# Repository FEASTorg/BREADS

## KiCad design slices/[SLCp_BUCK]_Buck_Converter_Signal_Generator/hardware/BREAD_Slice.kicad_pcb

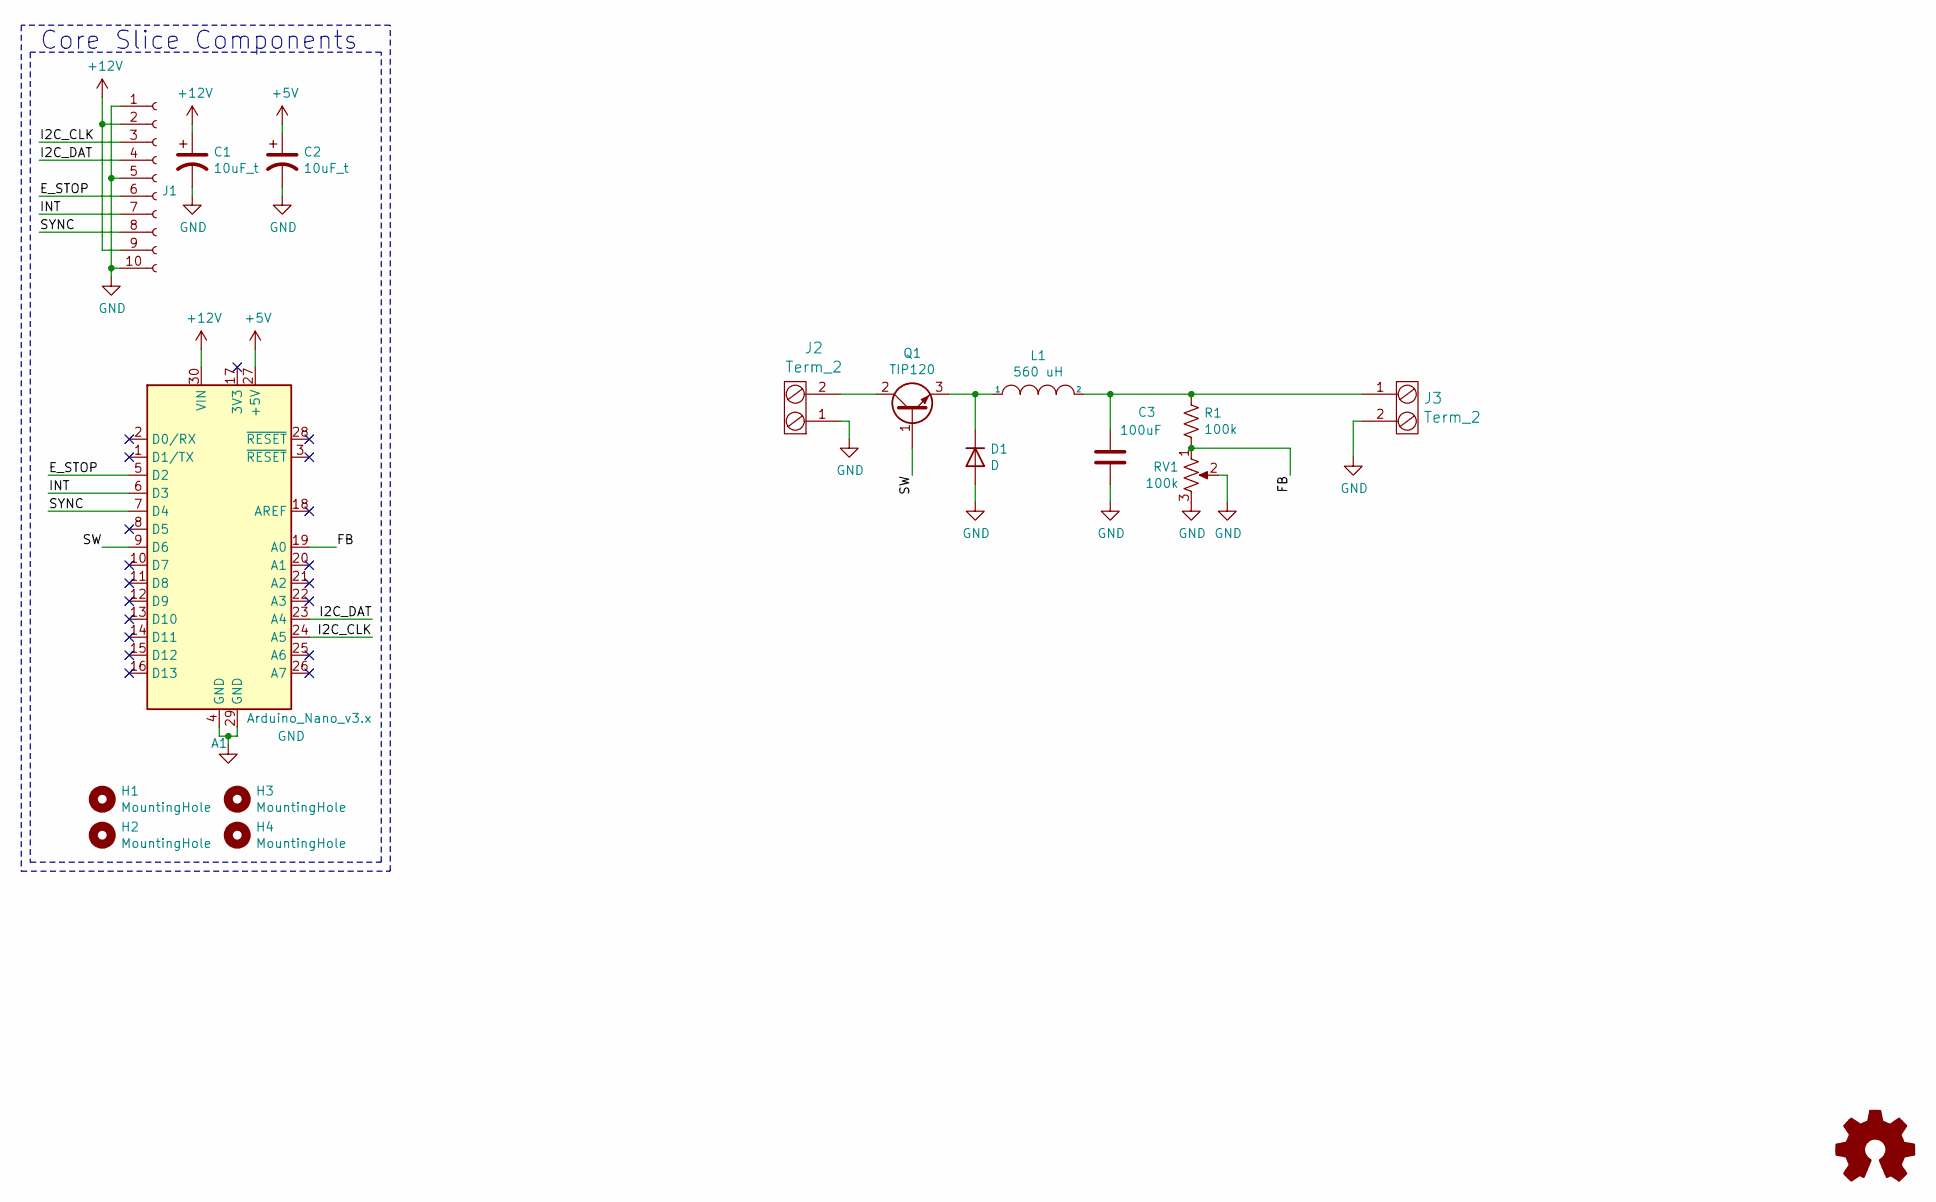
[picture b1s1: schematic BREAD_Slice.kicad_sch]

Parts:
A1: Arduino_Nano_v3.x; Arduino_Nano
C1, C2: 10uF_t; C_2312; Part # T491C106K025AT
C3: 100uF; C_Radial_D8_L11.5_P3.5
D1: D; Diode_DO-41_SOD81_Horizontal_RM10
H1, H2, H3, H4: MountingHole; MountingHole_3.2mm_M3_DIN965_Pad
J1: Conn_01x10_Female; PinSocket_1x10_P2.54mm_Horizontal
J2, J3: Term_2; TerminalBlock_Pheonix_MKDS1.5-2pol; Part # 1935161
L1: 560 uH; L_Radial_D28.0mm_P29.20mm
Logo1: Logo_Open_Hardware_Small; OSHW-Symbol_6.7x6mm_SilkScreen
Q1: TIP120; TO-220_Neutral123_Vertical_LargePads; Part # TIP120
R1: 100k; R_Axial_DIN0309_L9.0mm_D3.2mm_P15.24mm_Horizontal
RV1: 100k; Potentiometer_Bourns_3266W_Vertical

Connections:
+5V: A1.27 (+5V), C2.1
+12V: A1.30 (VIN), C1.1, J1.2, J1.9
/E_STOP: A1.5 (D2), J1.6
/FB: A1.19 (A0), R1.2, RV1.1
/I2C_CLK: A1.24 (A5), J1.3
/I2C_DAT: A1.23 (A4), J1.4
/INT: A1.6 (D3), J1.7
/SW: A1.9 (D6), Q1.1 (B)
/SYNC: A1.7 (D4), J1.8
GND: A1.4 (GND), A1.29 (GND), C1.2, C2.2, C3.2, D1.2 (A), J1.1, J1.5, J1.10, J2.1, J3.2, RV1.2, RV1.3
unnamed: C3.1, J3.1, L1.2, R1.1
unnamed: D1.1 (K), L1.1, Q1.3 (E)
unnamed: J2.2, Q1.2 (C)

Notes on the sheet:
Core Slice Components

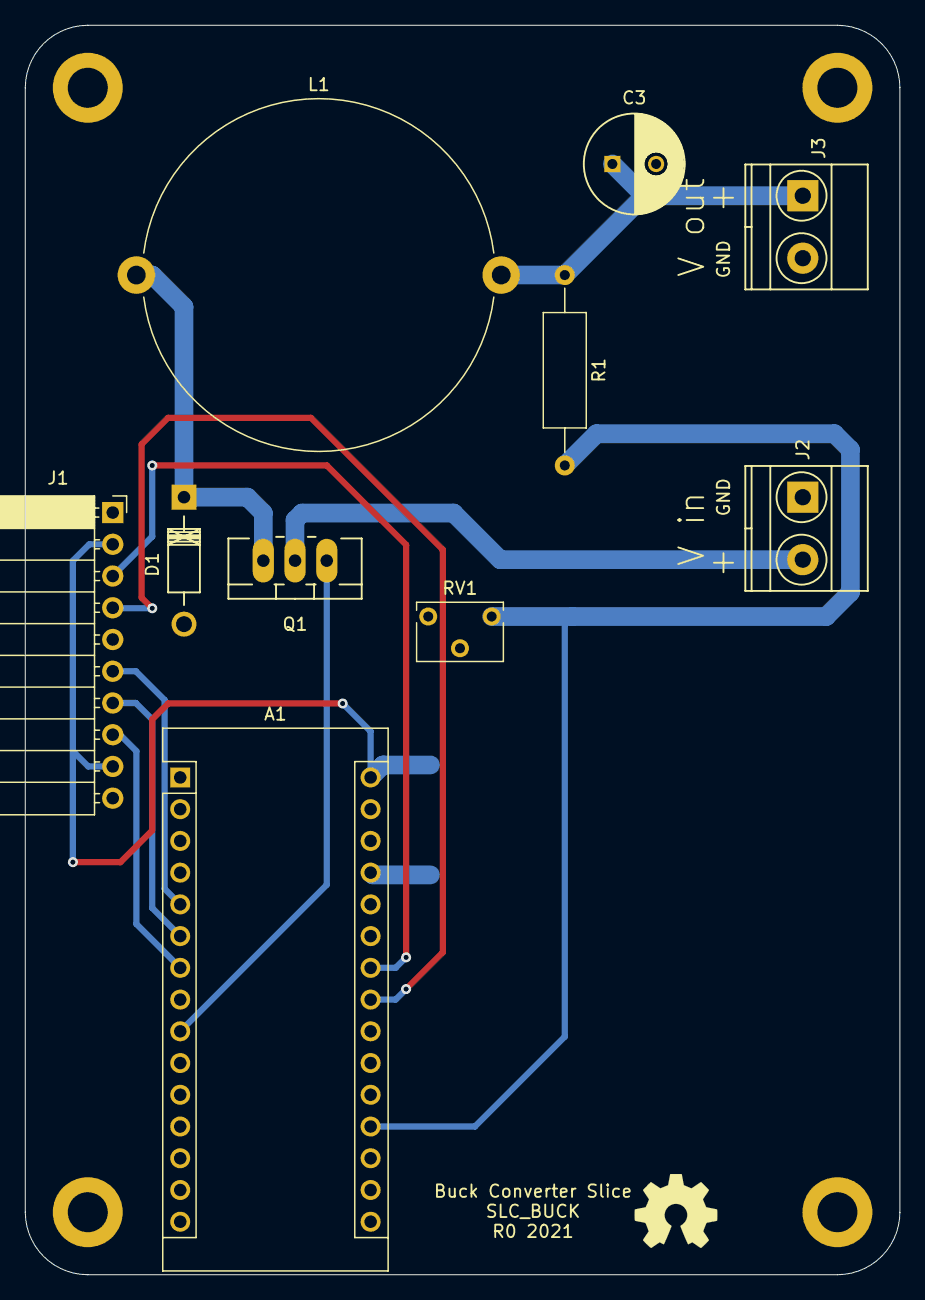
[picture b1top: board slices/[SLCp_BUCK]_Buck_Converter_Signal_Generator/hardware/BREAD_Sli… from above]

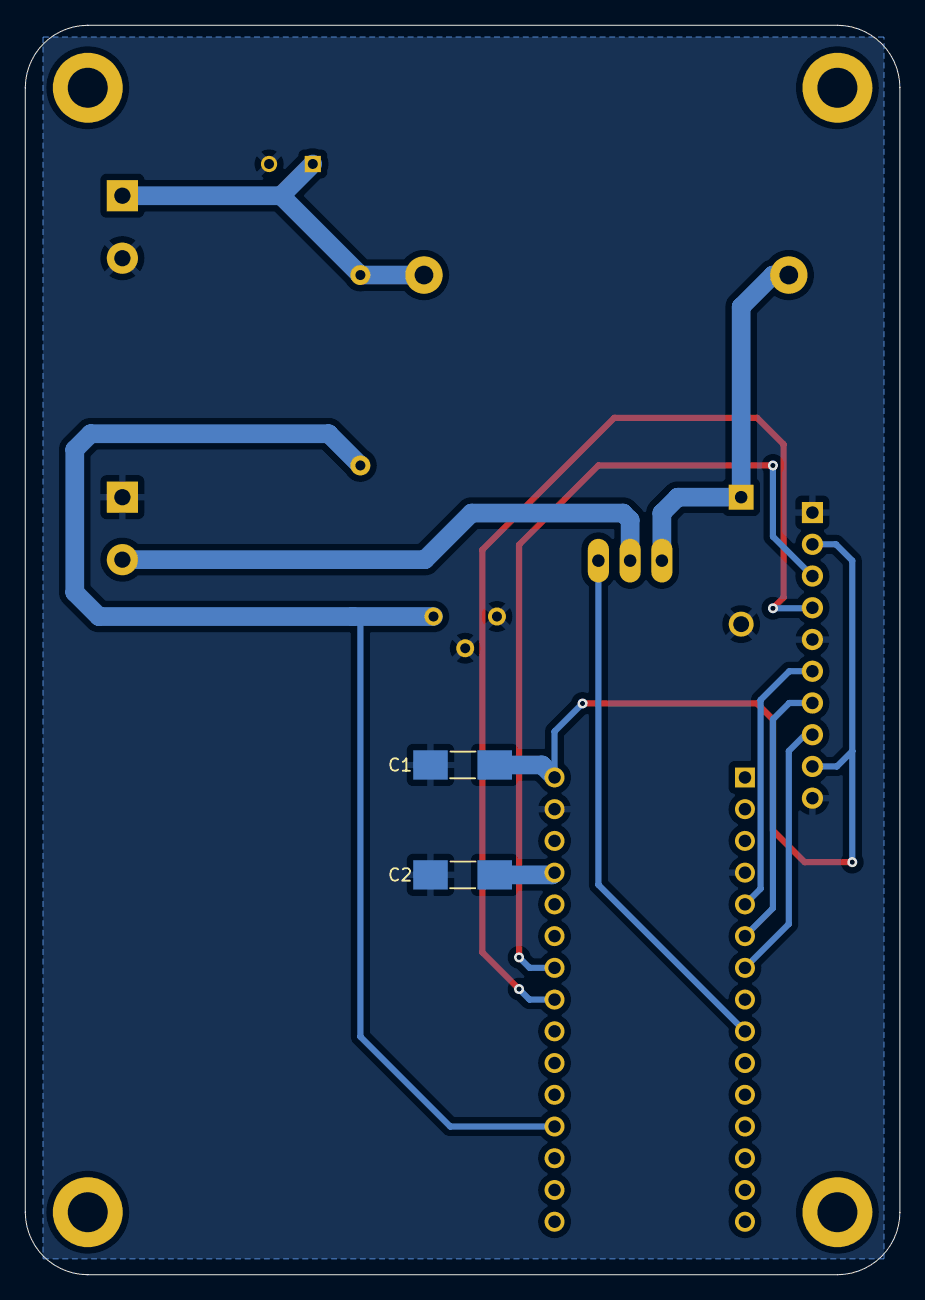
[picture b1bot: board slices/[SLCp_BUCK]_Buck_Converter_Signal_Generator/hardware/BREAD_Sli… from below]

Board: 2 copper layers, 70.0 x 100.0 mm, 17 parts (2 on the bottom side), 13 nets.

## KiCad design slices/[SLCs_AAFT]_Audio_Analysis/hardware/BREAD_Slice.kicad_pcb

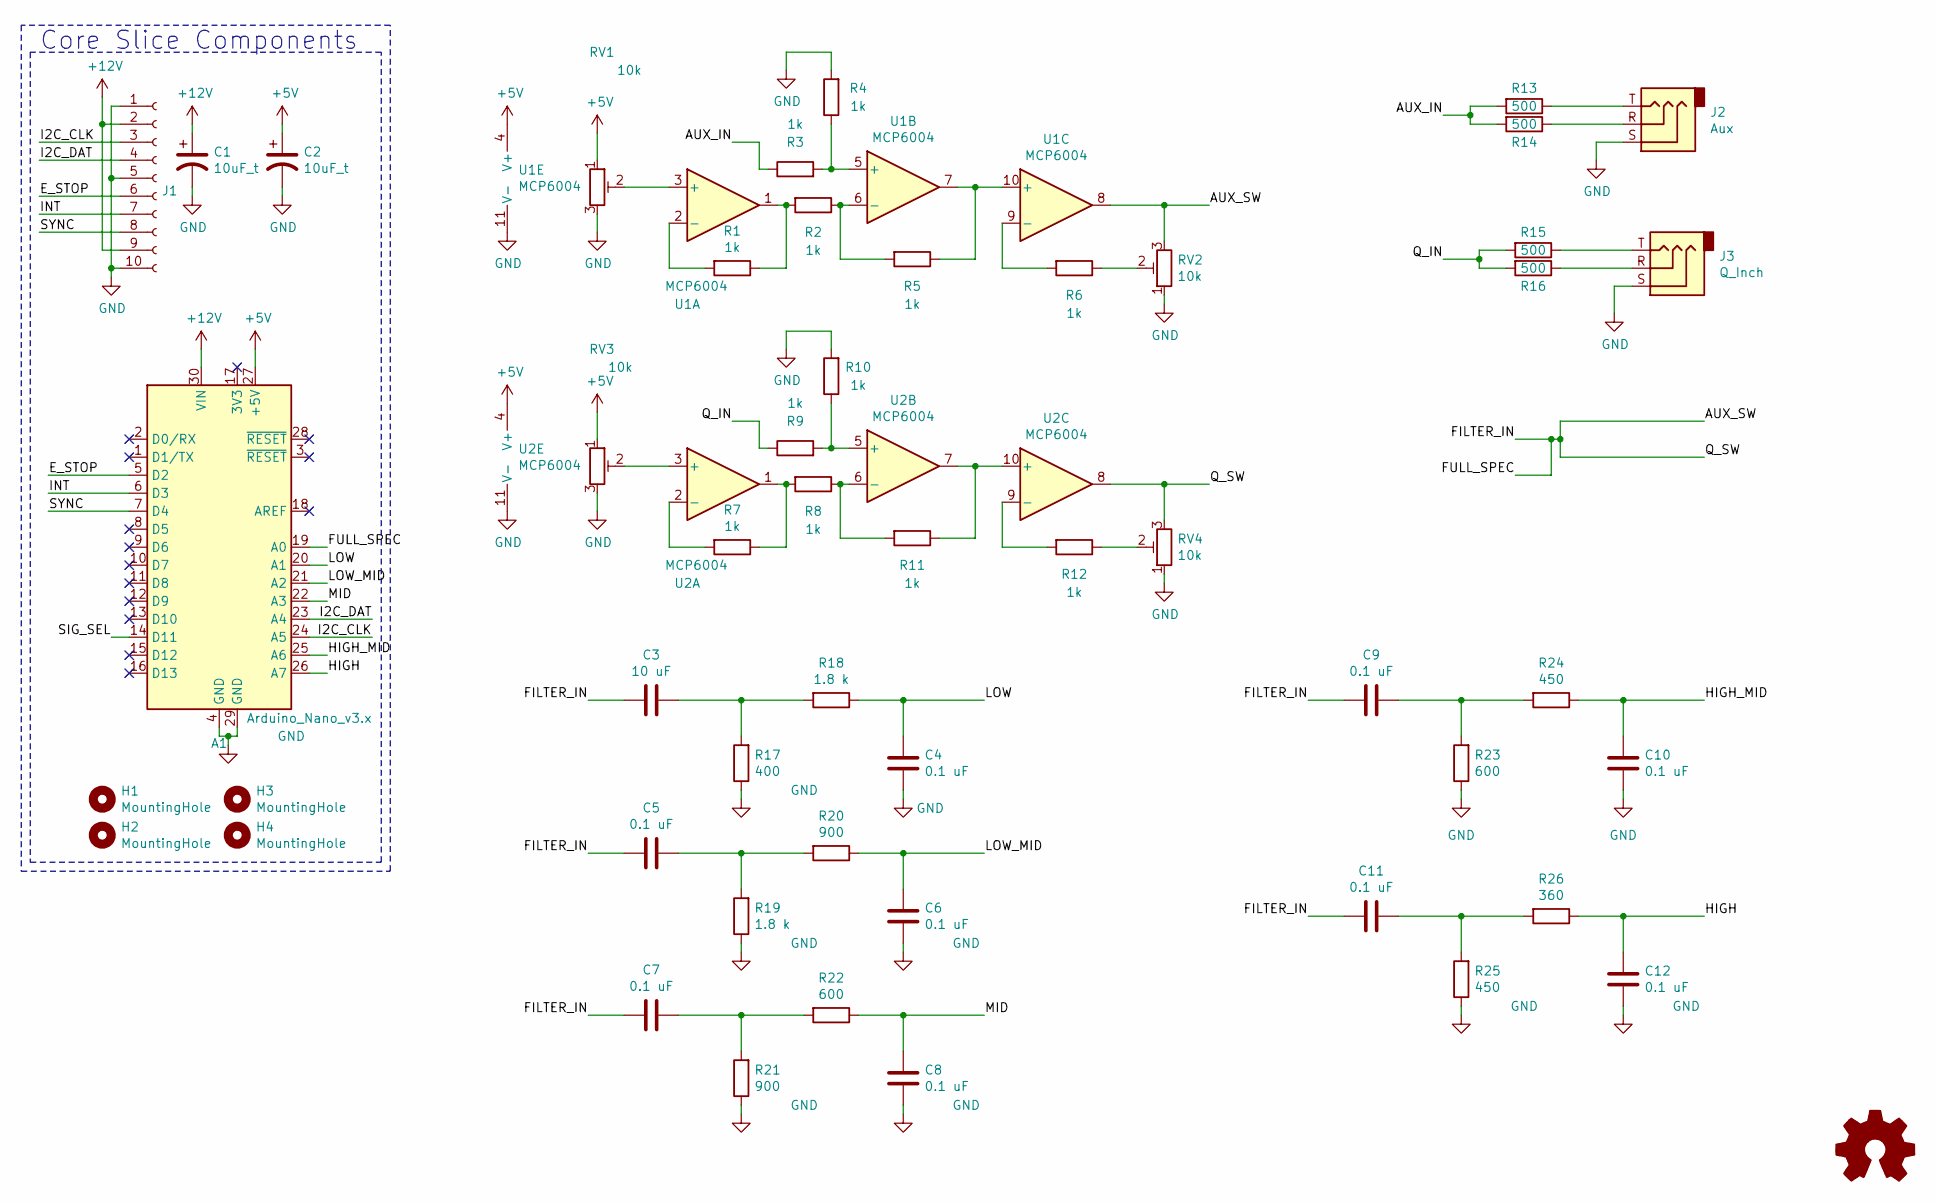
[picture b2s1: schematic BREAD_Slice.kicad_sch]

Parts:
A1: Arduino_Nano_v3.x; Arduino_Nano
C1, C2: 10uF_t; C_2312; Part # T491C106K025AT
C3: 10 uF; C_1206_3216Metric_Pad1.33x1.80mm_HandSolder
C4, C5, C6, C7, C8, C9, C10, C11, C12: 0.1 uF; C_1206_3216Metric_Pad1.33x1.80mm_HandSolder
H1, H2, H3, H4: MountingHole; MountingHole_3.2mm_M3_DIN965_Pad
J1: Conn_01x10_Female; PinSocket_1x10_P2.54mm_Horizontal
J2: Aux; Jack_3.5mm_CUI_SJ1-3533NG_Horizontal
J3: Q_Inch; Jack_6.35mm_Neutrik_NMJ6HCD2_Horizontal
Logo1: Logo_Open_Hardware_Small; OSHW-Symbol_6.7x6mm_SilkScreen
R1, R2, R3, R4, R5, R6, R7, R8, R9, R10, R11, R12: 1k; R_1206_3216Metric_Pad1.30x1.75mm_HandSolder
R13, R14, R15, R16: 500; R_1206_3216Metric_Pad1.30x1.75mm_HandSolder
R17: 400; R_1206_3216Metric_Pad1.30x1.75mm_HandSolder
R18, R19: 1.8 k; R_1206_3216Metric_Pad1.30x1.75mm_HandSolder
R20, R21: 900; R_1206_3216Metric_Pad1.30x1.75mm_HandSolder
R22, R23: 600; R_1206_3216Metric_Pad1.30x1.75mm_HandSolder
R24, R25: 450; R_1206_3216Metric_Pad1.30x1.75mm_HandSolder
R26: 360; R_1206_3216Metric_Pad1.30x1.75mm_HandSolder
RV1, RV2, RV3, RV4: 10k; Potentiometer_Bourns_3266W_Vertical
U1, U2: MCP6004; DIP-14_W7.62mm_Socket

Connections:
+5V: A1.27 (+5V), C2.1, RV1.1, RV3.1, U1.4 (V+), U2.4 (V+)
+12V: A1.30 (VIN), C1.1, J1.2, J1.9
/AUX_IN: R3.1, R13.2, R14.2
/AUX_SW: A1.19 (A0), C3.2, C5.2, C7.2, C9.2, C11.2, RV2.3, RV4.3, U1.8, U2.8
/E_STOP: A1.5 (D2), J1.6
/HIGH: A1.26 (A7), C12.2, R26.1
/HIGH_MID: A1.25 (A6), C10.2, R24.1
/I2C_CLK: A1.24 (A5), J1.3
/I2C_DAT: A1.23 (A4), J1.4
/INT: A1.6 (D3), J1.7
/LOW: A1.20 (A1), C4.2, R18.1
/LOW_MID: A1.21 (A2), C6.2, R20.1
/MID: A1.22 (A3), C8.2, R22.1
/Q_IN: R9.1, R15.2, R16.2
/SIG_SEL: A1.14 (D11)
/SYNC: A1.7 (D4), J1.8
GND: A1.4 (GND), A1.29 (GND), C1.2, C2.2, C4.1, C6.1, C8.1, C10.1, C12.1, J1.1, J1.5, J1.10, J2.S, J3.S, R4.2, R10.2, R17.1, R19.1, R21.1, R23.1, R25.1, RV1.3, RV2.1, RV3.3, RV4.1, U1.11 (V-), U2.11 (V-)
unnamed: C3.1, R17.2, R18.2
unnamed: C5.1, R19.2, R20.2
unnamed: C7.1, R21.2, R22.2
unnamed: C9.1, R23.2, R24.2
unnamed: C11.1, R25.2, R26.2
unnamed: J2.R, R14.1
unnamed: J2.T, R13.1
unnamed: J3.R, R16.1
unnamed: J3.T, R15.1
unnamed: R1.1, R2.2, U1.1
unnamed: R1.2, U1.2 (-)
unnamed: R2.1, R5.2, U1.6 (-)
unnamed: R3.2, R4.1, U1.5 (+)
unnamed: R5.1, U1.7, U1.10 (+)
unnamed: R6.1, RV2.2
unnamed: R6.2, U1.9 (-)
unnamed: R7.1, R8.2, U2.1
unnamed: R7.2, U2.2 (-)
unnamed: R9.2, R10.1, U2.5 (+)
unnamed: R11.1, U2.7, U2.10 (+)
unnamed: R8.1, R11.2, U2.6 (-)
unnamed: R12.1, RV4.2
unnamed: R12.2, U2.9 (-)
unnamed: RV1.2, U1.3 (+)
unnamed: RV3.2, U2.3 (+)

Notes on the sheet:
Core Slice Components

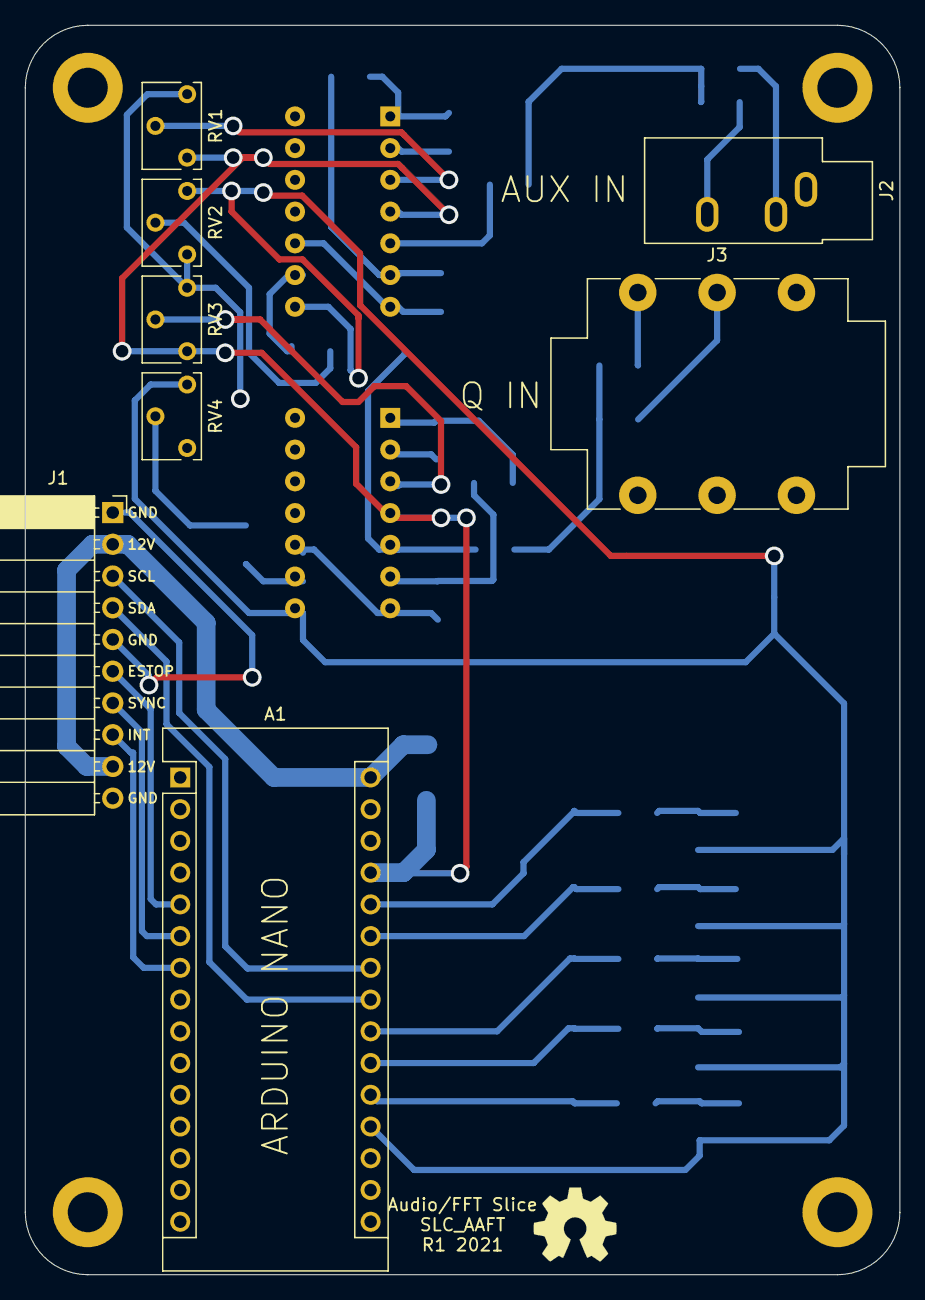
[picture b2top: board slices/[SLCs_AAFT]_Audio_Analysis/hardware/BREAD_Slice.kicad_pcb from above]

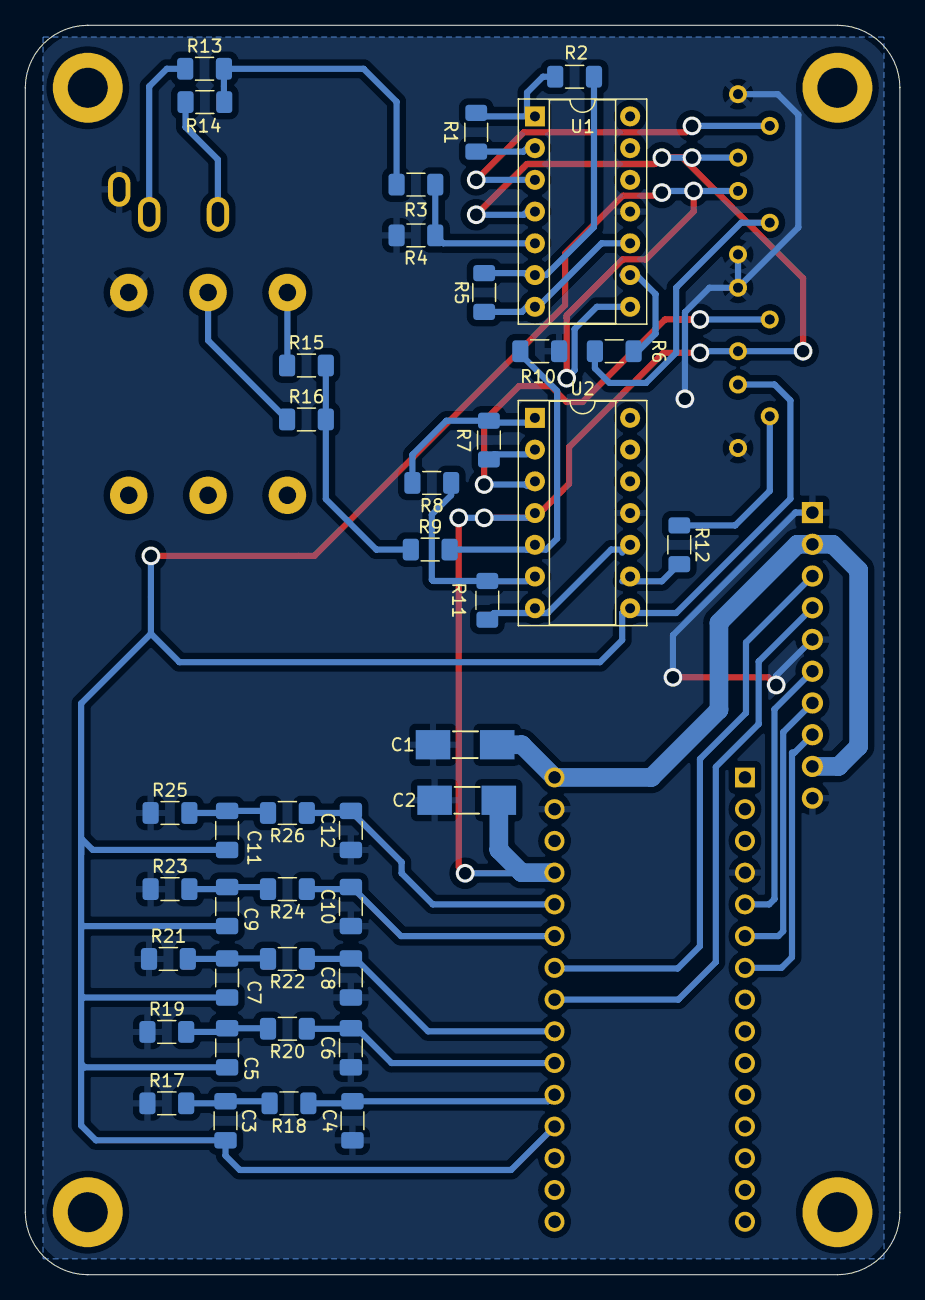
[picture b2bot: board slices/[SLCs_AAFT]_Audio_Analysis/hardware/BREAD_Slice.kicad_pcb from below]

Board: 2 copper layers, 70.0 x 100.0 mm, 53 parts (40 on the bottom side), 41 nets.

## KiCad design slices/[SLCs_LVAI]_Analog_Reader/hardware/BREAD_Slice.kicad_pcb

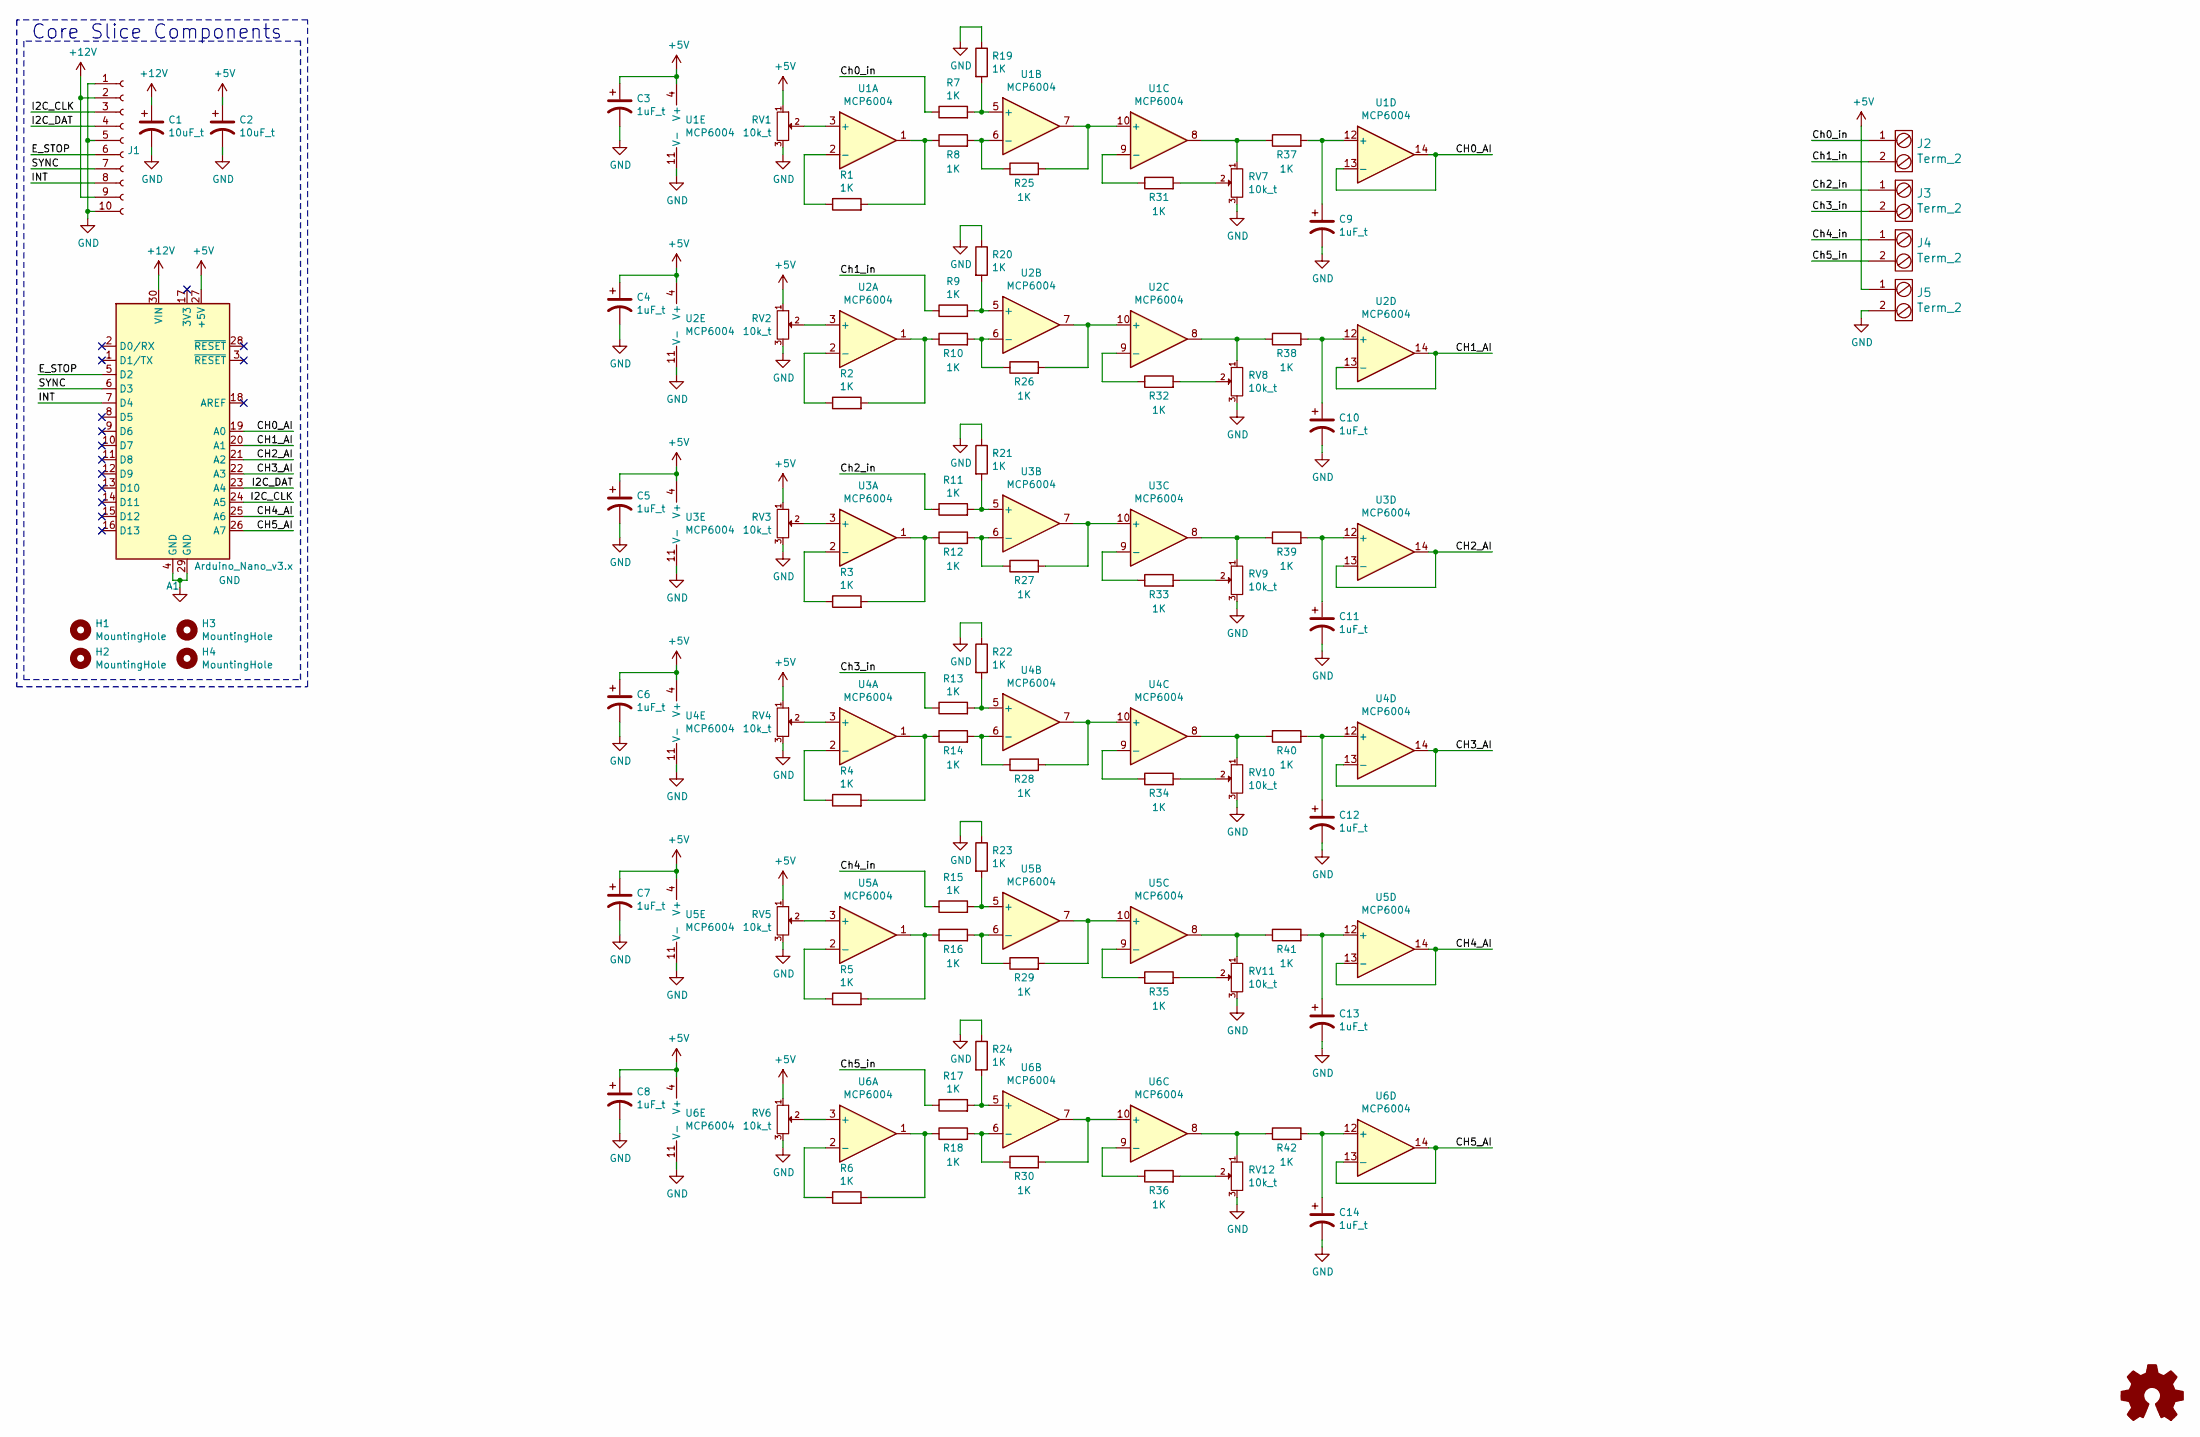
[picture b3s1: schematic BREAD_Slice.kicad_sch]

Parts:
A1: Arduino_Nano_v3.x; Arduino_Nano
C1, C2: 10uF_t; C_2312; Part # T491C106K025AT
C3, C4, C5, C6, C7, C8, C9, C10, C11, C12, C13, C14: 1uF_t; C_1206_HandSoldering; Part # T491A105K025AT
H1, H2, H3, H4: MountingHole; MountingHole_3.2mm_M3_DIN965_Pad
J1: Conn_01x10_Female; PinSocket_1x10_P2.54mm_Horizontal
J2, J3, J4, J5: Term_2; TerminalBlock_Pheonix_MKDS1.5-2pol; Part # 1935161
Logo1: Logo_Open_Hardware_Small; OSHW-Symbol_6.7x6mm_SilkScreen
R1, R2, R3, R4, R5, R6, R7, R8, R9, R10, R11, R12, R13, R14, R15, R16, R17, R18, R19, R20, R21, R22, R23, R24, R25, R26, R27, R28, R29, R30, R31, R32, R33, R34, R35, R36, R37, R38, R39, R40, R41, R42: 1K; R_1206_HandSoldering; Part # RC1206FR-071KL
RV1, RV2, RV3, RV4, RV5, RV6, RV7, RV8, RV9, RV10, RV11, RV12: 10k_t; Potentiometer_Bourns_3296W_3-8Zoll_Inline_ScrewUp; Part # 1-1623849-0
U1, U2, U3, U4, U5, U6: MCP6004; DIP-14_W7.62mm_Socket_LongPads

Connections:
+5V: A1.27 (+5V), C2.1, C3.1, C4.1, C5.1, C6.1, C7.1, C8.1, J5.1, RV1.1, RV2.1, RV3.1, RV4.1, RV5.1, RV6.1, U1.4 (V+), U2.4 (V+), U3.4 (V+), U4.4 (V+), U5.4 (V+), U6.4 (V+)
+12V: A1.30 (VIN), C1.1, J1.2, J1.9
/CH0_AI: A1.19 (A0), U1.13 (-), U1.14
/CH1_AI: A1.20 (A1), U2.13 (-), U2.14
/CH2_AI: A1.21 (A2), U3.13 (-), U3.14
/CH3_AI: A1.22 (A3), U4.13 (-), U4.14
/CH4_AI: A1.25 (A6), U5.13 (-), U5.14
/CH5_AI: A1.26 (A7), U6.13 (-), U6.14
/Ch0_in: J2.1, R7.1
/Ch1_in: J2.2, R9.1
/Ch2_in: J3.1, R11.1
/Ch3_in: J3.2, R13.1
/Ch4_in: J4.1, R15.1
/Ch5_in: J4.2, R17.1
/E_STOP: A1.5 (D2), J1.6
/I2C_CLK: A1.24 (A5), J1.3
/I2C_DAT: A1.23 (A4), J1.4
/INT: A1.7 (D4), J1.8
/SYNC: A1.6 (D3), J1.7
GND: A1.4 (GND), A1.29 (GND), C1.2, C2.2, C3.2, C4.2, C5.2, C6.2, C7.2, C8.2, C9.2, C10.2, C11.2, C12.2, C13.2, C14.2, J1.1, J1.5, J1.10, J5.2, R19.1, R20.1, R21.1, R22.1, R23.1, R24.1, RV1.3, RV2.3, RV3.3, RV4.3, RV5.3, RV6.3, RV7.3, RV8.3, RV9.3, RV10.3, RV11.3, RV12.3, U1.11 (V-), U2.11 (V-), U3.11 (V-), U4.11 (V-), U5.11 (V-), U6.11 (V-)
unnamed: C9.1, R37.2, U1.12 (+)
unnamed: C10.1, R38.2, U2.12 (+)
unnamed: C11.1, R39.2, U3.12 (+)
unnamed: C12.1, R40.2, U4.12 (+)
unnamed: C13.1, R41.2, U5.12 (+)
unnamed: C14.1, R42.2, U6.12 (+)
unnamed: R1.1, U1.2 (-)
unnamed: R1.2, R8.1, U1.1
unnamed: R2.1, U2.2 (-)
unnamed: R3.1, U3.2 (-)
unnamed: R4.1, U4.2 (-)
unnamed: R5.1, U5.2 (-)
unnamed: R6.1, U6.2 (-)
unnamed: R2.2, R10.1, U2.1
unnamed: R10.2, R26.1, U2.6 (-)
unnamed: R11.2, R21.2, U3.5 (+)
unnamed: R3.2, R12.1, U3.1
unnamed: R12.2, R27.1, U3.6 (-)
unnamed: R13.2, R22.2, U4.5 (+)
unnamed: R4.2, R14.1, U4.1
unnamed: R14.2, R28.1, U4.6 (-)
unnamed: R15.2, R23.2, U5.5 (+)
unnamed: R5.2, R16.1, U5.1
unnamed: R16.2, R29.1, U5.6 (-)
unnamed: R17.2, R24.2, U6.5 (+)
unnamed: R6.2, R18.1, U6.1
unnamed: R18.2, R30.1, U6.6 (-)
unnamed: R7.2, R19.2, U1.5 (+)
unnamed: R9.2, R20.2, U2.5 (+)
unnamed: R8.2, R25.1, U1.6 (-)
unnamed: R25.2, U1.7, U1.10 (+)
unnamed: R26.2, U2.7, U2.10 (+)
unnamed: R27.2, U3.7, U3.10 (+)
unnamed: R28.2, U4.7, U4.10 (+)
unnamed: R29.2, U5.7, U5.10 (+)
unnamed: R30.2, U6.7, U6.10 (+)
unnamed: R31.1, U1.9 (-)
unnamed: R31.2, RV7.2
unnamed: R32.1, U2.9 (-)
unnamed: R32.2, RV8.2
unnamed: R33.1, U3.9 (-)
unnamed: R33.2, RV9.2
unnamed: R34.1, U4.9 (-)
unnamed: R34.2, RV10.2
unnamed: R35.1, U5.9 (-)
unnamed: R35.2, RV11.2
unnamed: R36.1, U6.9 (-)
unnamed: R36.2, RV12.2
unnamed: R37.1, RV7.1, U1.8
unnamed: R38.1, RV8.1, U2.8
unnamed: R39.1, RV9.1, U3.8
unnamed: R40.1, RV10.1, U4.8
unnamed: R41.1, RV11.1, U5.8
unnamed: R42.1, RV12.1, U6.8
unnamed: RV1.2, U1.3 (+)
unnamed: RV2.2, U2.3 (+)
unnamed: RV3.2, U3.3 (+)
unnamed: RV4.2, U4.3 (+)
unnamed: RV5.2, U5.3 (+)
unnamed: RV6.2, U6.3 (+)

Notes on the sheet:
Core Slice Components

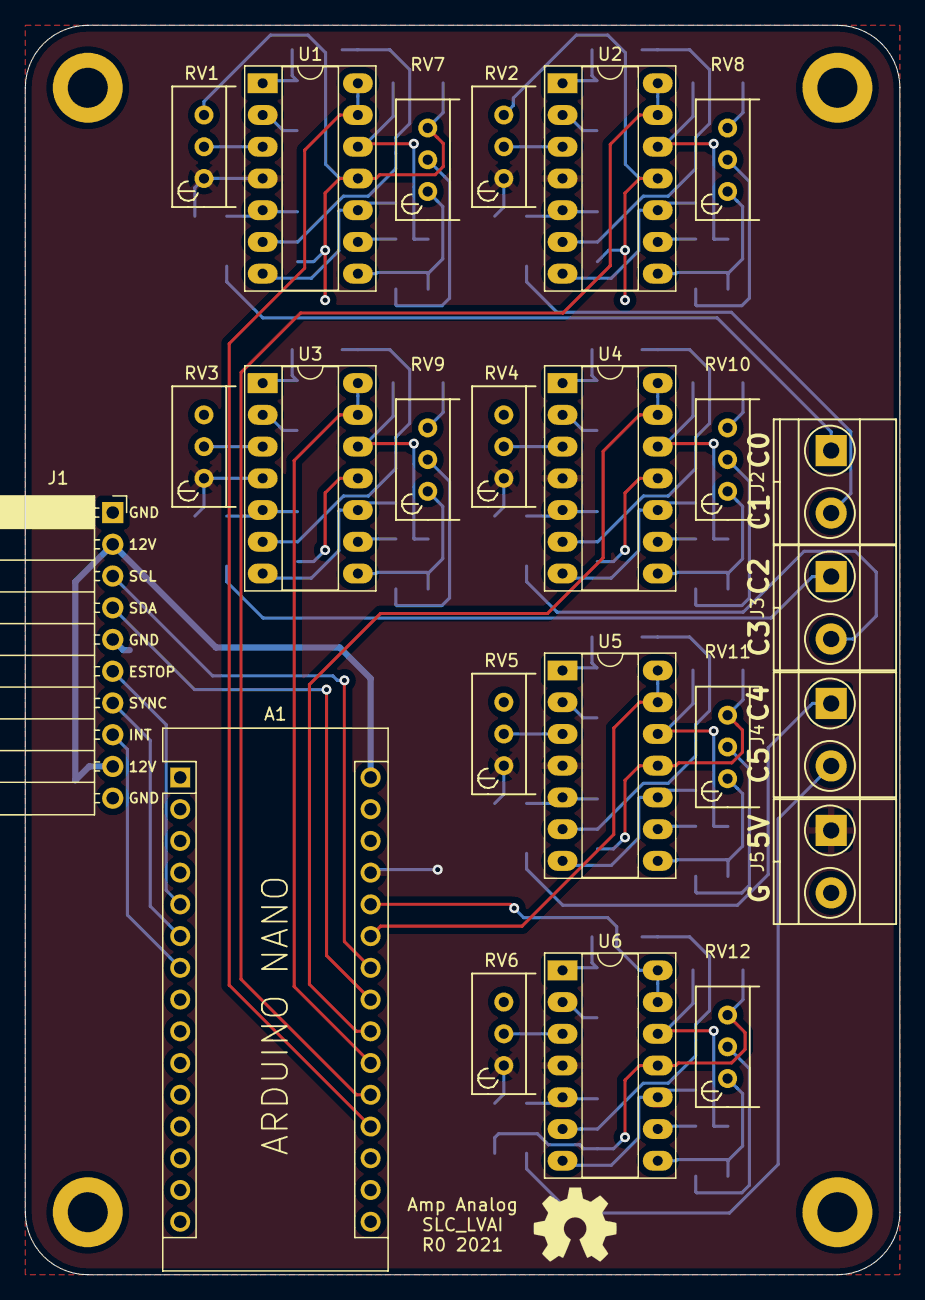
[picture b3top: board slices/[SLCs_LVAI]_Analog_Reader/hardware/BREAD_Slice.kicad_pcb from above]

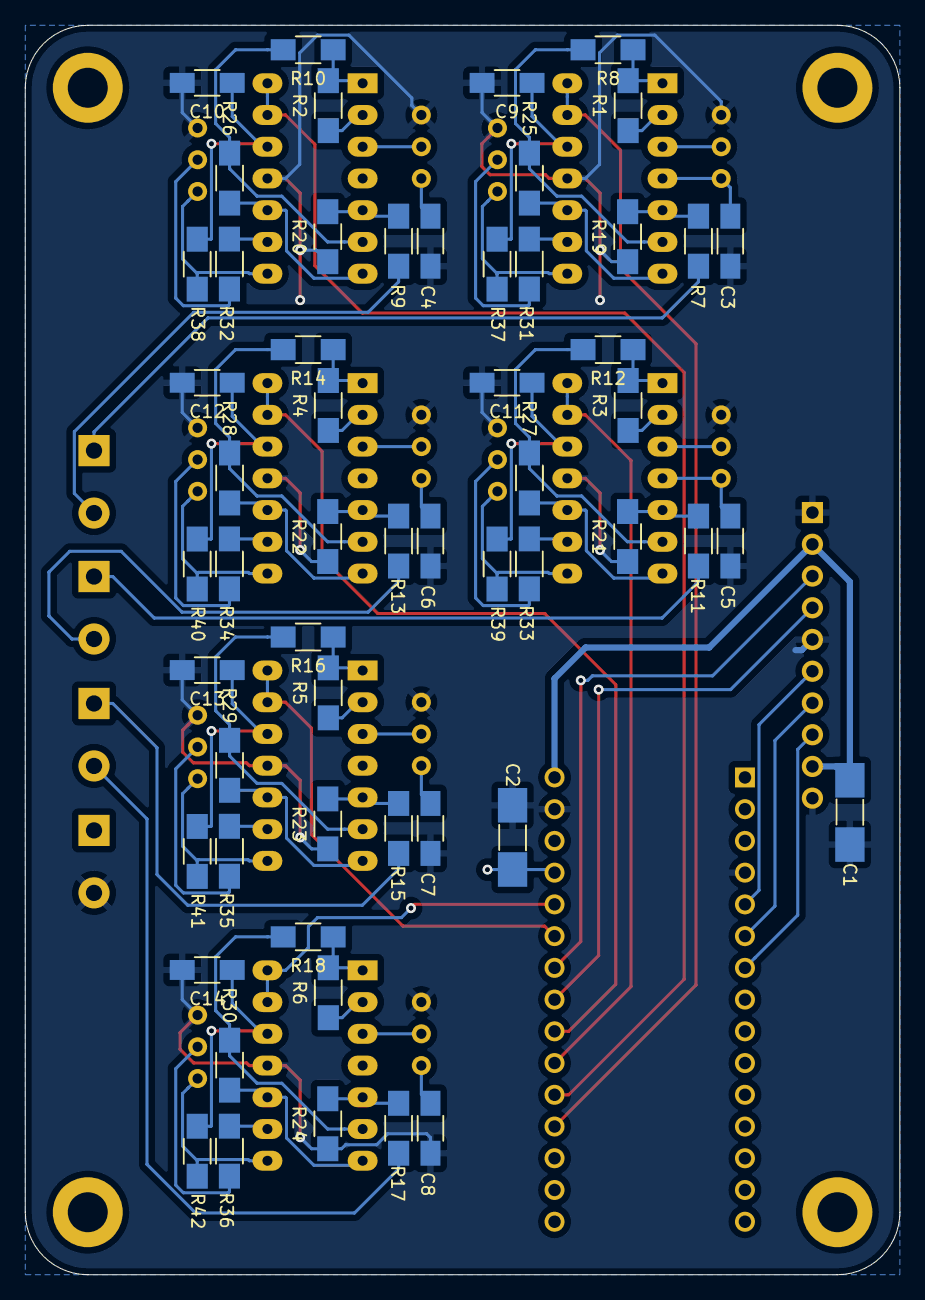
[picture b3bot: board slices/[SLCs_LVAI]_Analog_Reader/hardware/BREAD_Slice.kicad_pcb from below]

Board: 2 copper layers, 70.0 x 100.0 mm, 85 parts (56 on the bottom side), 80 nets.
